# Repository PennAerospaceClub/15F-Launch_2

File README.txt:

README flight-2

Implementing guided descent.

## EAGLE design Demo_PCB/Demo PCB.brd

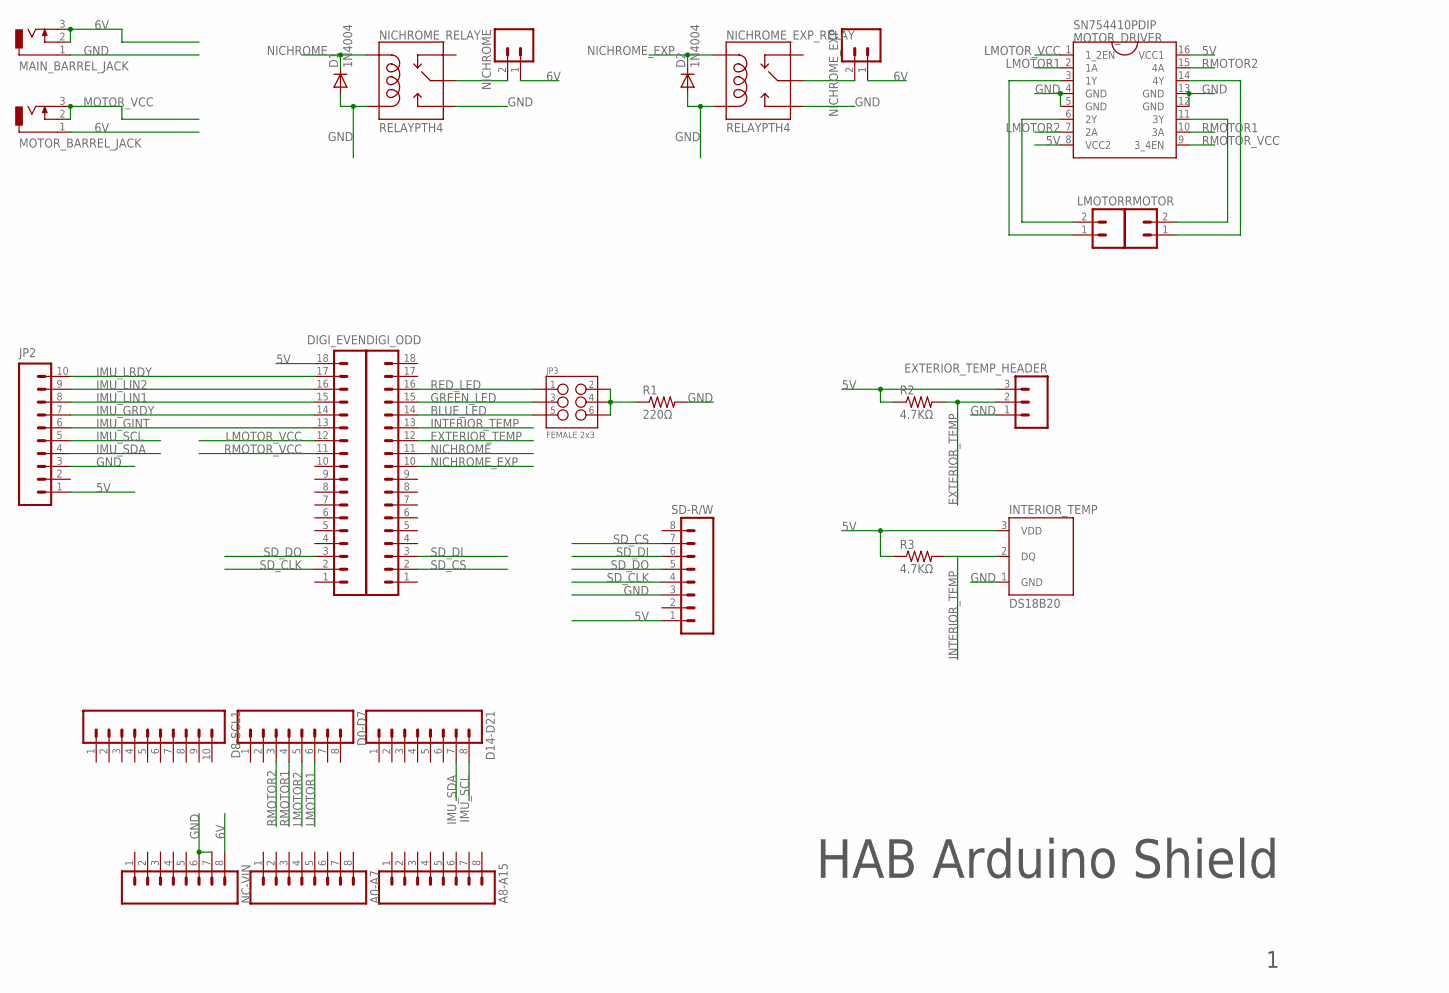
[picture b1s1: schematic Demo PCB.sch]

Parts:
A0-A7, A8-A15: M08; 1X08_ROUND
D0-D7, D14-D21: M08; 1X08_ROUND
D1, D2: 1N4004; DO41-10
D8-SCL1: M10SILK_FEMALE_PTH; 1X10
DIGI_EVEN: M18_; 1X18
DIGI_ODD: M18_; 1X18
EXTERIOR_TEMP_HEADER: M03PTH; 1X03
INTERIOR_TEMP: DS18B20; TO-92-AMMO
JP2: M10SILK_FEMALE_PTH; 1X10
JP3: FEMALE 2x3; 2X3
LMOTOR: M02PTH; 1X02
MAIN_BARREL_JACK: DCJ0303
MOTOR_BARREL_JACK: DCJ0303
MOTOR_DRIVER: SN754410PDIP; DIL16
NC-VIN: M08; 1X08_ROUND
NICHROME: M02PTH; 1X02
NICHROME_EXP: M02PTH; 1X02
NICHROME_EXP_RELAY: RELAYPTH4; RELAY-JZC
NICHROME_RELAY: RELAYPTH4; RELAY-JZC
R1: 220Ω; 0204/7
R2, R3: 4.7KΩ; 0204/7
RMOTOR: M02PTH; 1X02
SD-R/W: M08; 1X08_ROUND

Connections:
5V: DIGI_EVEN.18, EXTERIOR_TEMP_HEADER.3, INTERIOR_TEMP.3 (VDD), JP2.1, MOTOR_DRIVER.8 (VCC2), MOTOR_DRIVER.16 (VCC1), R2.1, R3.1, SD-R/W.1
6V: MAIN_BARREL_JACK.2, MAIN_BARREL_JACK.3, MOTOR_BARREL_JACK.1, NC-VIN.8, NICHROME.1, NICHROME_EXP.1
BLUE_LED: DIGI_ODD.14, JP3.5
EXTERIOR_TEMP: DIGI_ODD.12, EXTERIOR_TEMP_HEADER.2, R2.2
GND: D1.A, D2.A, EXTERIOR_TEMP_HEADER.1, INTERIOR_TEMP.1 (GND), JP2.3, MAIN_BARREL_JACK.1, MOTOR_DRIVER.4 (GND), MOTOR_DRIVER.5 (GND), MOTOR_DRIVER.12 (GND), MOTOR_DRIVER.13 (GND), NC-VIN.6, NC-VIN.7, NICHROME_EXP_RELAY.1 (COIL2), NICHROME_EXP_RELAY.3 (NO), NICHROME_RELAY.1 (COIL2), NICHROME_RELAY.3 (NO), R1.2, SD-R/W.3
GREEN_LED: DIGI_ODD.15, JP3.3
IMU_GINT: DIGI_EVEN.13, JP2.6
IMU_GRDY: DIGI_EVEN.14, JP2.7
IMU_LIN1: DIGI_EVEN.15, JP2.8
IMU_LIN2: DIGI_EVEN.16, JP2.9
IMU_LRDY: DIGI_EVEN.17, JP2.10
IMU_SCL: D14-D21.8, JP2.5
IMU_SDA: D14-D21.7, JP2.4
INTERIOR_TEMP: DIGI_ODD.13
LMOTOR1: D0-D7.6, MOTOR_DRIVER.2 (1A)
LMOTOR2: D0-D7.5, MOTOR_DRIVER.7 (2A)
LMOTOR_VCC: DIGI_EVEN.12, MOTOR_DRIVER.1 (1_2EN)
MOTOR_VCC: MOTOR_BARREL_JACK.2, MOTOR_BARREL_JACK.3
unnamed: INTERIOR_TEMP.2 (DQ), R3.2
unnamed: NICHROME_EXP.2, NICHROME_EXP_RELAY.4 (MAIN)
unnamed: MOTOR_DRIVER.11 (3Y), RMOTOR.2
unnamed: MOTOR_DRIVER.14 (4Y), RMOTOR.1
unnamed: JP3.2, JP3.4, JP3.6, R1.1
unnamed: LMOTOR.2, MOTOR_DRIVER.6 (2Y)
unnamed: LMOTOR.1, MOTOR_DRIVER.3 (1Y)
unnamed: NICHROME.2, NICHROME_RELAY.4 (MAIN)
NICHROME: D1.C, DIGI_ODD.11, NICHROME_RELAY.5 (COIL1)
NICHROME_EXP: D2.C, DIGI_ODD.10, NICHROME_EXP_RELAY.5 (COIL1)
RED_LED: DIGI_ODD.16, JP3.1
RMOTOR1: D0-D7.4, MOTOR_DRIVER.10 (3A)
RMOTOR2: D0-D7.3, MOTOR_DRIVER.15 (4A)
RMOTOR_VCC: DIGI_EVEN.11, MOTOR_DRIVER.9 (3_4EN)
SD_CLK: DIGI_EVEN.2, SD-R/W.4
SD_CS: DIGI_ODD.2, SD-R/W.7
SD_DI: DIGI_ODD.3, SD-R/W.6
SD_DO: DIGI_EVEN.3, SD-R/W.5

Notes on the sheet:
HAB Arduino Shield

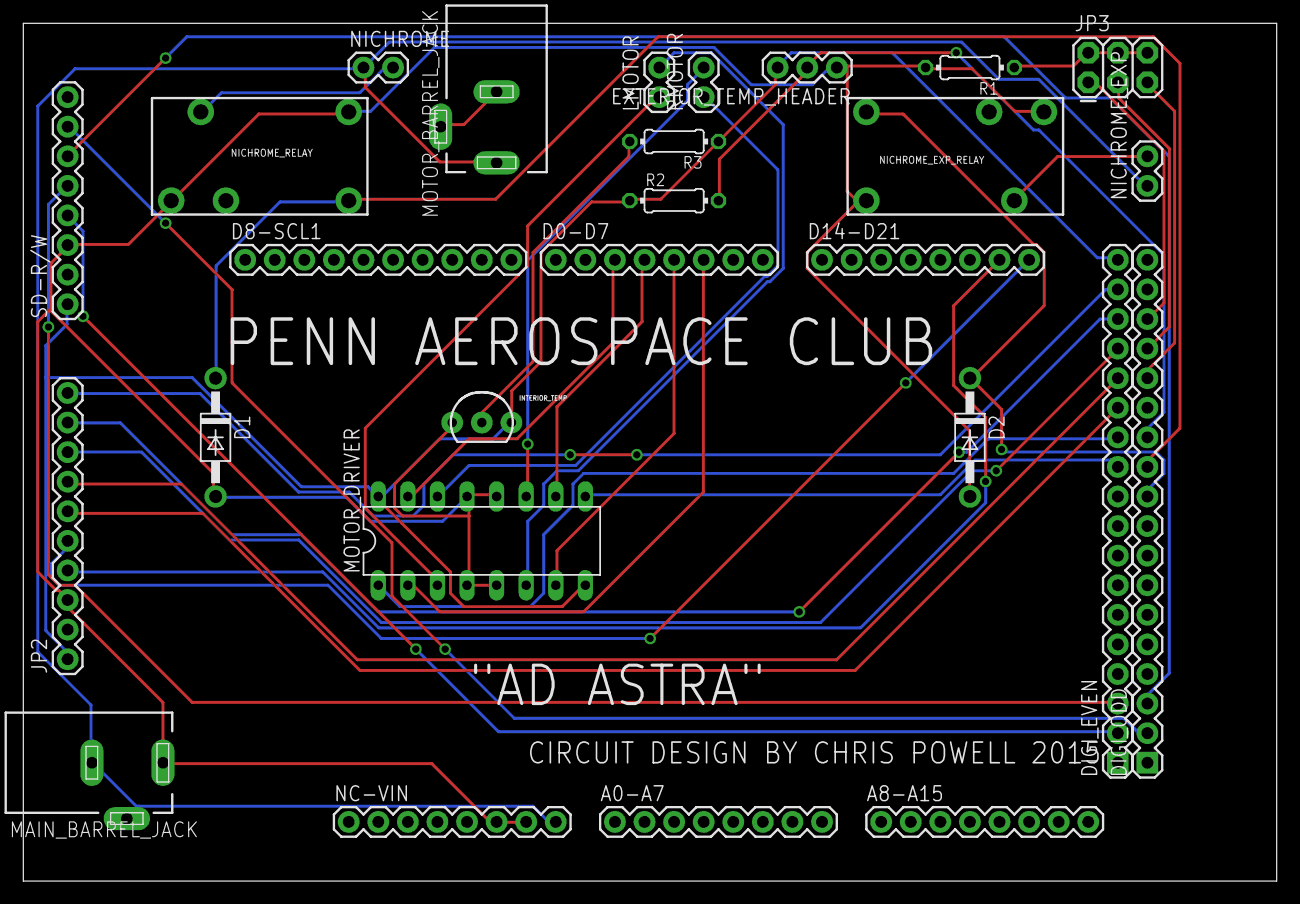
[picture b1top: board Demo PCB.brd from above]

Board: 2 copper layers, 107.6 x 73.7 mm, 27 parts (0 on the bottom side), 35 nets.

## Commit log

2015-11-12 Eagle Files for PCB
    Create Eagle .brd and .sch for potential PCB shield
2015-11-17 Add frame and title block to .sch, new idea for nichrome
2015-11-20 Change MOSFETS to Relays + Finalize Board
2015-11-21 added seperate SD writing and trackuino
2015-11-21 added clocks
2015-11-22 Added Readme v1
2015-11-22 Broke up original Flight Code into file specific functions, cleaned
2015-11-22 Updated initial Sanity, Implemented Smoothing, All related rewrites to fit this new system.
2015-11-22 Rename Mega_Flight_Integration_V1_with_SD_write.ino to Main.ino
2015-11-22 Rename Main.ino to Mega_Flight_Integration_V1_with_SD_write.ino
2015-11-22 added two way serial and handshake
2015-11-22 fixed the serial reading
2015-11-22 In testing rn, lots of debugging comments, trying to get serial communications up
2015-11-22 changing to send gps data 2 back and includes serial tests
2015-11-25 Fixed Arduino Serial Communication by using Mega's Hardware serial. All code is in debugging mode rn. Need to implement handshake correctly, and keep uno code from continuing until handshake occurs. 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
2015-11-25 Added two way serial comms for trackuino and fixed issue with incoming serial reading
2015-11-25 changed updateMaxAlt to use smAlt
2015-12-03 changed naming conventions
2015-12-03 Updated Due Serial Test
2015-12-03 mega serial testing update
2015-12-03 fixed weird header errors
2015-12-03 working on integrated seial handshake
2015-12-03 fixing serial handshake
2015-12-03 Signing off, further down serial testing
2015-12-04 working GPS on mega code
2015-12-04 trackuino is working with this version
2015-12-04 works with two way Mega comms and gps
2015-12-04 working handshake
2015-12-04 halfway through passing imu code, check out concat
2015-12-06 Inter-arduino serial debugging
2015-12-09 Includes working trackuino code. Serial integration is in older trackuino integration files
2015-12-11 New Launch Code: Rewrote how gps is interfaced, integrated IMU, integrated SD, integrated sanity, integrated LEDS
2015-12-11 fixed read string. Works with the Mega now and sends dynamic IMU data
2015-12-14 Final Flight Code

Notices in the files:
parts and their libraries:
SparkFun-Connectors: Licensing: Creative Commons ShareAlike 4.0 International - https://creativecommons.org/licenses/by-sa/4.0
